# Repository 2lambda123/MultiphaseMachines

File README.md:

# Multiphase-Machine Testbench

This repository contains software code and documentation for deployment at the experiemental multiphase-machine (WICSC) testbench at the SPL at KTH.

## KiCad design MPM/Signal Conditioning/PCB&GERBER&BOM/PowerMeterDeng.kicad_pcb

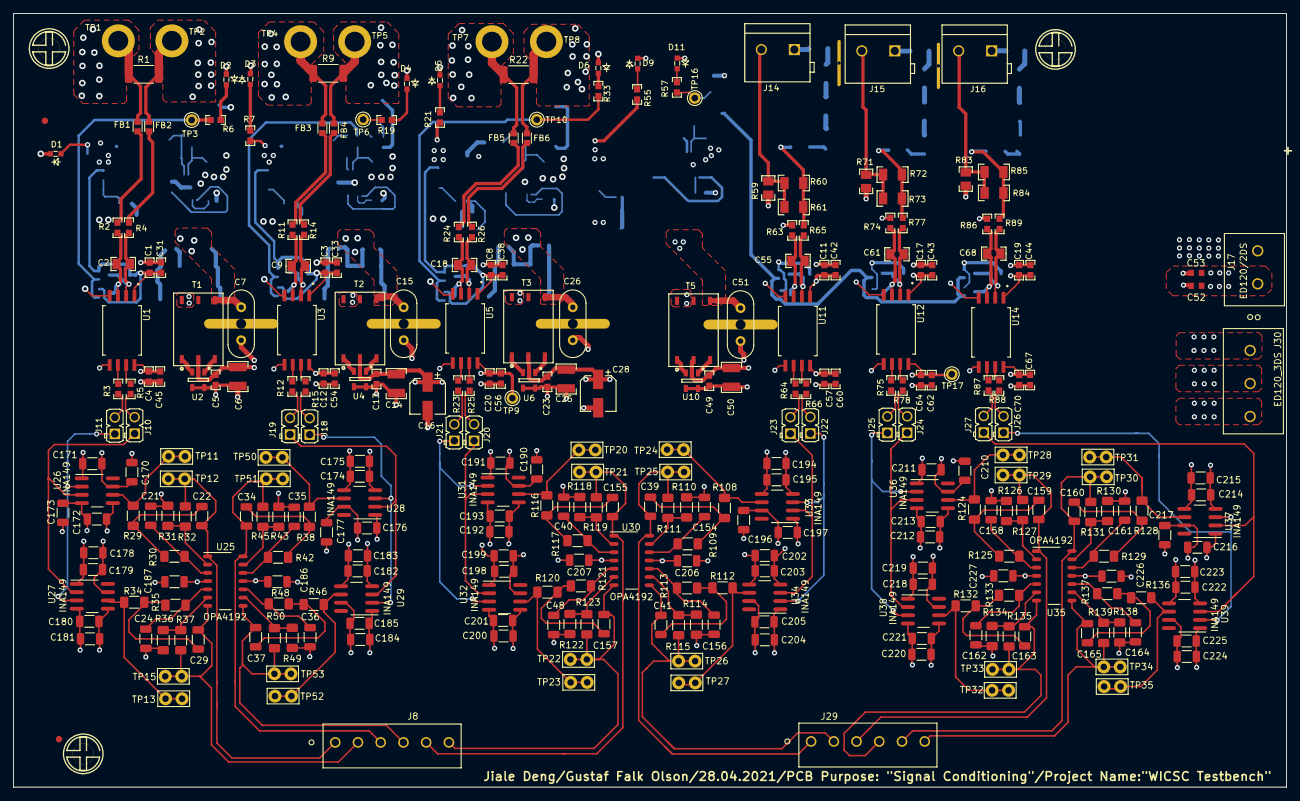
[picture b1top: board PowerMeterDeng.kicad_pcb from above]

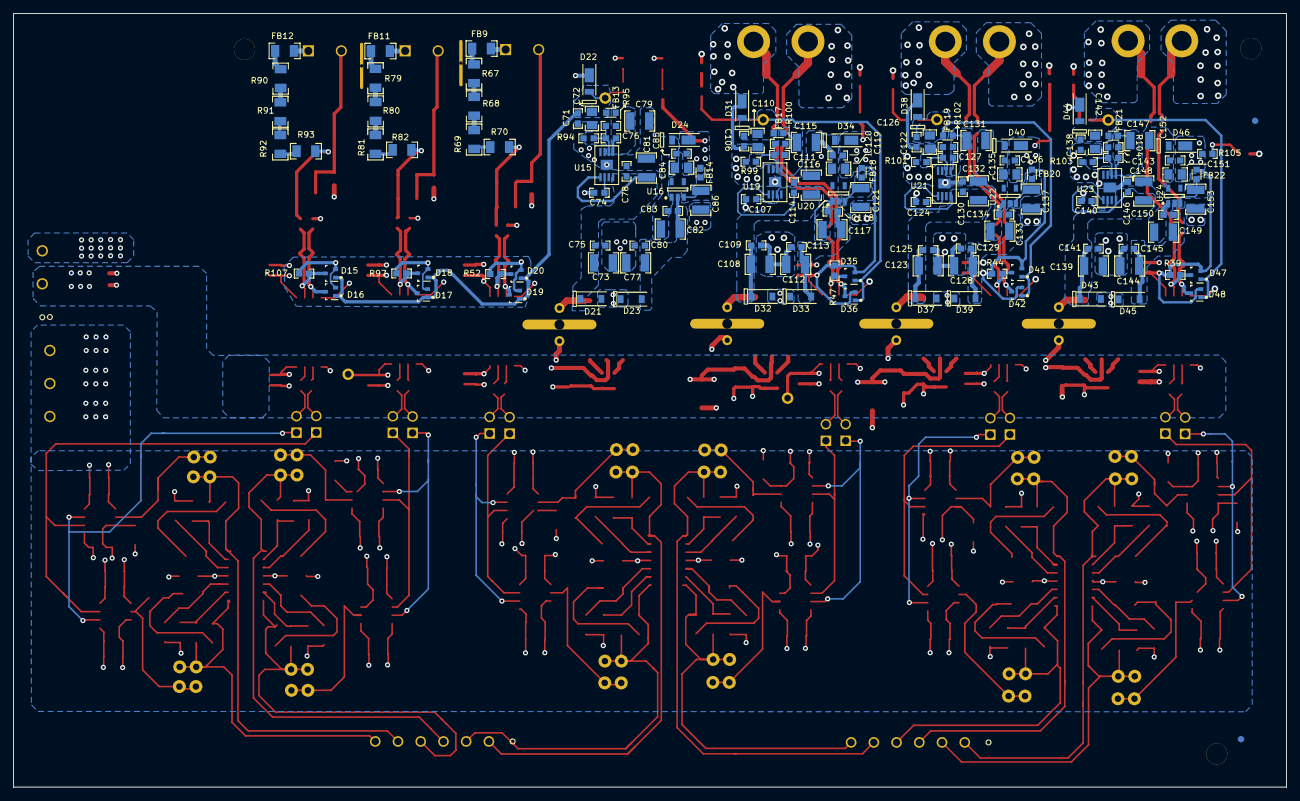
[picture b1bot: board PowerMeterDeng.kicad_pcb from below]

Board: 4 copper layers, 196.0 x 119.1 mm, 459 parts (140 on the bottom side), 197 nets.

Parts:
C1: 0603_19
C2: 08055A331KAT2A; 0805_HV_1
C3: 0603_18
C4: 0603_86
C5: 0603_89
C6: 1210_24
C7: CAP_200mil_2
C8: 0603_87
C9: 08055A331KAT2A; 0805_HV_13
C11: 0603_66
C12: 0603_95
C13: 0603_20
C14: 1210_25
C15: CAP_200mil_3
C16: UUD1E220MCL1GS; SM_RADIAL_5MM_2
C17: 0603_81
C18: 08055A331KAT2A; 0805_HV_15
C19: 0603_88
C20, C64: 0603_63
C21, C24, C35, C36, C40, C48, C154, C156, C158, C161, C162, C164: 100p; C_1206_3216Metric
C22, C29, C34, C37, C155, C157: 105p; C_1206_3216Metric
C23: 0603_13
C25: 1210_2
C26: CAP_200mil_1
C28: UUD1E220MCL1GS; SM_RADIAL_5MM_1
C31: GRM188R71C105KA12D; 0603_10
C33: GRM188R71C105KA12D; 0603_9
C38, C45: GRM188R71C105KA12D; 0603_6
C39, C41, C159, C160, C163, C165: 110p; C_1206_3216Metric
C42, C43: GRM188R71C105KA12D; 0603_8
C44: GRM188R71C105KA12D; 0603_7
C49: 0603_90
C50: 1210_26
C51: CAP_200mil_4
C52: 0.1uF; 06033C104JAT2A
C53: 4.7uF; 0603ZD475KAT2A
C54: GRM188R71C105KA12D; 0603_5
C55: 08055A331KAT2A; 0805_HV_9
C56: GRM188R71C105KA12D; 0603_4
C57: 0603_85
C60: GRM188R71C105KA12D; 0603_3
C61: 08055A331KAT2A; 0805_HV_10
C62: GRM188R71C105KA12D; 0603_2
C67: GRM188R71C105KA12D; 0603_1
C68: 08055A331KAT2A; 0805_HV_11
C70: 0603_67
C71: 0603_40
C72: 0805_HV_6
C73: 1210_23
C74: 0603_41
C75, C80, C83: 0603_31
C76: 0603_8
C77: 1210_22
C78: 0603_38
C79: 1210_17
C81: 1210_16
C82: 1210_18
C84: 0805_HV_7
C85: 0603_42
C86: 1210_19
C106, C145, C150: 0603_16
C107: 0603_100
C108: 1210_21
C109: 0603_60
C110: 0805_HV_17
C111: 0603_99
C112: 1210_3
C113: 0603_62
C114: 0603_98
C115: 1210_27
C116: 1210_20
C117: 1210_28
C118: 0603_102
C119: 0805_HV_18
C120: 0603_101
C121: 1210_29
C122: 0603_34
C123: 1210_7
C124: 0603_35
C125: 0603_22
C126: 0805_HV_4
C127: 0603_33
C128: 1210_5
C129: 0603_17
C130: 0603_32
C131: 1210_13
C132: 1210_12
C133: 1210_14
C134: 0603_37
C135: 0805_HV_5
C136: 0603_36
C137: 1210_15
C138: 0603_25
C139: 1210_6
C140: 0603_26
C141: 0603_21
C142: 0805_HV_2
C143: 0603_24
C144: 1210_4
C146: 0603_23
C147: 1210_9
C148: 1210_8
C149: 1210_10
C151: 0805_HV_3
C152: 0603_27
C153: 1210_11
C170, C173, C175, C176, C178, C181, C182, C184, C186, C187, C190, C193, C195, C196, C198, C201, C202, C204, C206, C207, C210, C213, C215, C216, C218, C221, C222, C224, C226, C227: 100nF; C_1206_3216Metric
C171, C172, C174, C177, C179, C180, C183, C185, C191, C192, C194, C197, C199, C200, C203, C205, C211, C212, C214, C217, C219, C220, C223, C225: 1uF; C_1206_3216Metric
D1: LED0603AA_3
D2: LED0603AA_1
D3: LED0603AA_5
D4: LED0603AA_4
D5: LED0603AA_9
D6: LED0603AA_2
D9: LED0603AA_7
D11: LED0603AA_6
D15: SOT-323_11
D16: SOT-323_12
D17: SOT-323_8
D18: SOT-323_6
D19: SOT-323_7
D20: SOT-323_5
D21: MBR0520L; SOD-123_8
D22: powerDI123_6
D23: MBR0520L; SOD-123_7
D24: powerDI123_7
D31: powerDI123_1
D32: MBR0520L; SOD-123_2
D33: MBR0520L; SOD-123_1
D34: powerDI123_8
D35: SOT-323_2
D36: SOT-323_1
D37: MBR0520L; SOD-123_6
D38: powerDI123_4
D39: MBR0520L; SOD-123_5
D40: powerDI123_5
D41: SOT-323_9
D42: SOT-323_10
D43: MBR0520L; SOD-123_4
D44: powerDI123_2
D45: MBR0520L; SOD-123_3
D46: powerDI123_3
D47: SOT-323_3
D48: SOT-323_4
FB1: MMZ1608B102C; FB0603_8
FB2, FB3, FB4: MMZ1608B102C; FB0603_9
FB5: MMZ1608B102C; FB0603_11
FB6: MMZ1608B102C; FB0603_10
FB9: ERJ-8ENF3323V; 1206_2
FB11: ERJ-8ENF3323V; 1206_3
FB12: ERJ-8ENF3323V; 1206_4
FB13: FB0603_6
FB14: FB0603_7
FB17: FB0603_1
FB18: FB0603_12
FB19: FB0603_4
FB20: FB0603_5
FB21: FB0603_2
FB22: FB0603_3
FID1, FID2, FID5, FID6: Fiducial10-20_1
J8, J29: Conn_01x06; ED555&slash_6DS
J10, J22, J23, J24, J25, J26, J27: 61300211121; WURTH_61300211121_1
J11: 61300211121; WURTH_61300211121_6
J14: ED120/2DS; CONN_ED120-2DS_2
J15: ED120/2DS; CONN_ED120-2DS_3
J16: ED120/2DS; CONN_ED120-2DS_1
J17: ED120/2DS; ED120&slash_2DS
J18: 61300211121; WURTH_61300211121_5
J19: 61300211121; WURTH_61300211121_4
J20: 61300211121; WURTH_61300211121_3
J21: 61300211121; WURTH_61300211121_2
J30: ED120_3DS; ED120&slash_3DS
LOGO1: TI_STACKED_SOLDERMASK_SMALL_1
MH1, MH2, MH3: MH3.2_1
R1, R9, R22: R_2010_5025Metric
R2, R4: RC0603FR-0712RL; 0603_46
R3, R5, R6, R7: 0603_49
R11, R14: RC0603FR-0712RL; 0603_58
R12, R15: 0603_47
R19, R33: 0603_53
R21: 0603_107
R23, R25: 0603_44
R24: RC0603FR-0712RL; 0603_91
R26: RC0603FR-0712RL; 0603_59
R29, R34, R38, R46, R116, R120: 3.01k; R_1206_3216Metric_Pad1.30x1.75mm_HandSolder
R30, R35, R42, R48, R117, R121: 16.5k; R_1206_3216Metric_Pad1.30x1.75mm_HandSolder
R31, R36, R43, R49, R118, R122: 2.49k; R_1206_3216Metric_Pad1.30x1.75mm_HandSolder
R32, R37, R45, R50, R119, R123: 7.5k; R_1206_3216Metric_Pad1.30x1.75mm_HandSolder
R39, R97: CRCW0603160KFKEA; 0603_53
R44: CRCW0603160KFKEA; 0603_8
R47: CRCW0603160KFKEA; 0603_82
R52: CRCW0603160KFKEA; 0603_111
R55, R75, R87, R88: 0603_57
R57: 0603_55
R59: CRCW08050000Z0EA; 0805_HV_8
R60: RC1206FR-071K02L; 1206_8
R61: RC1206FR-072K4L; 1206_9
R63, R65, R77: RC0603FR-0712RL; 0603_64
R64, R66, R78: 0603_64
R67: ERJ-8ENF3323V; 1206_1
R68: ERJ-8ENF3323V; 1206_5
R69: ERJ-8ENF3323V; 1206_6
R70: ERJ-8ENF3323V; 1206_7
R71: CRCW08050000Z0EA; 0805_HV_12
R72: RC1206FR-071K02L; 1206_14
R73: RC1206FR-072K4L; 1206_15
R74: RC0603FR-0712RL; 0603_57
R79: ERJ-8ENF3323V; 1206_10
R80: ERJ-8ENF3323V; 1206_11
R81: ERJ-8ENF3323V; 1206_12
R82: ERJ-8ENF3323V; 1206_13
R83: CRCW08050000Z0EA; 0805_HV_16
R84: RC1206FR-071K02L; 1206_20
R85: RC1206FR-072K4L; 1206_7
R86: RC0603FR-0712RL; 0603_92
R89: RC0603FR-0712RL; 0603_65
R90: ERJ-8ENF3323V; 1206_16
R91: ERJ-8ENF3323V; 1206_17
R92: ERJ-8ENF3323V; 1206_18
R93: ERJ-8ENF3323V; 1206_19
R94: 0603_56
R95: RC0603FR-073K16L; 0603_56
R99: 0603_106
R100: RC0603FR-073K16L; 0603_24
R101: 0603_54
R102: RC0603FR-073K16L; 0603_33
R103: 0603_51
R104: RC0603FR-073K16L; 0603_50
R105: 0603_52
R107: CRCW0603160KFKEA; 0603_112
R108, R112, R124, R128, R132, R136: 1.35k; R_1206_3216Metric_Pad1.30x1.75mm_HandSolder
R109, R113, R125, R129, R133, R137: 17.8k; R_1206_3216Metric_Pad1.30x1.75mm_HandSolder
R110, R114, R126, R130, R134, R138: 500; R_1206_3216Metric_Pad1.30x1.75mm_HandSolder
R111, R115, R127, R131, R135, R139: 4k; R_1206_3216Metric_Pad1.30x1.75mm_HandSolder
T1: 750342271; 760390015_2
T2: 750342271; 760390015_3
T3: 750342271; 760390015_1
T5: 750342271; 760390015_4
TP1: TP-5001-BLACK; TH-40_2
TP2: TP-5001-BLACK; TH-40_1
TP3: TP-040_RND_1
TP4: TP-5001-BLACK; TH-40_4
TP5: TP-5001-BLACK; TH-40_3
TP6: TP-040_RND_2
TP7: TP-5001-BLACK; TH-40_6
TP8: TP-5001-BLACK; TH-40_5
TP9: TP-040_RND_5
TP10: TP-040_RND_4
TP11, TP12, TP13, TP15, TP20, TP21, TP22, TP23, TP24, TP25, TP26, TP27, TP28, TP29, TP30, TP31, TP32, TP33, TP34, TP35, TP50, TP51, TP52, TP53: TestPoint_Bridge_Pitch2.54mm_Drill1.0mm
TP16: TP-040_RND_3
TP17: TP-040_RND_6
U1, U3, U5, U11, U12, U14: AMC1300BDWVR
U2: SN6501DBV; DBV0005A_N_5
U4: SN6501DBV; DBV0005A_N_6
U6: SN6501DBV; DBV0005A_N_4
U10: SN6501DBV; DBV0005A_N_7
U15: MSOP8(DGN)_4
U16: TLV70450DBV; DBV0005A_N_3
U19: MSOP8(DGN)_1
U20: TLV70450DBV; DBV0005A_N_8
U21: MSOP8(DGN)_3
U22: TLV70450DBV; DBV0005A_N_2
U23: TPS7A3001DGNR; MSOP8(DGN)_2
U24: TLV70450DBV; DBV0005A_N_1
U25, U30, U35: OPA4192; OPA4192ID
U26, U27, U28, U29, U31, U32, U33, U34, U36, U37, U38, U39: INA149; INA149AIDR

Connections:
+5.0V_PH: C11.1, C17.1, C19.1, C42.2, C43.2, C44.2, C84.2, C85.1, D15.2, D16.2, D17.2, D18.2, D19.2, D20.2, D24.1, FB14.2, R52.2, R55.2, R97.2, R107.2, U11.1, U12.1, U14.1
+5.0V_USH: C1.1, C31.2, C151.2, C152.1, D46.1, D47.2, D48.2, FB22.2, R39.2, R105.2, U1.1
+5.0V_VSH: C3.1, C33.2, C135.2, C136.1, D40.1, D41.2, D42.2, FB20.2, R7.2, R44.2, U3.1
+5.0V_WSH: C8.1, C38.2, C119.2, C120.1, D34.1, D35.2, D36.2, FB18.2, R21.2, R47.2, U5.1
+5V_CNTL: C5.2, C6.2, C13.2, C14.2, C16.1, C23.2, C25.2, C28.1, C49.2, C50.2, C52.1, C53.1, J17.1, T1.2, T2.2, T3.2, T5.2, U2.2, U4.2, U6.2, U10.2
+6V_PH: C77.1, C80.1, C82.2, C83.1, D23.1, U16.2
+6V_USH: C144.1, C145.1, C149.2, C150.1, D45.1, U24.2
+6V_VSH: C128.1, C129.1, C133.2, C134.1, D39.1, U22.2
+6V_WSH: C112.1, C113.1, C117.2, C118.1, D33.1, U20.2
+15V: C172.1, C173.1, C174.1, C175.1, C180.1, C181.1, C182.1, C183.1, C187.1, C192.1, C193.1, C194.1, C195.1, C200.1, C201.1, C202.1, C203.1, C207.1, C212.1, C213.1, C214.1, C215.1, C220.1, C221.1, C222.1, C223.1, C227.1, J30.1, U25.4 (V+), U26.4, U27.4, U28.4, U29.4, U30.4 (V+), U31.4, U32.4, U33.4, U34.4, U35.4 (V+), U36.4, U37.4, U38.4, U39.4
-5.0V_PH: C71.1, C72.2, D15.1, D16.1, D17.1, D18.1, D19.1, D20.1, D22.2, FB13.2, R57.2, TP16.1
-5.0V_USH: C138.1, C142.2, D44.2, D47.1, D48.1, FB21.2, R6.2, TP3.1
-5.0V_VSH: C122.1, C126.2, D38.2, D41.1, D42.1, FB19.2, R19.2, TP6.1
-5.0V_WSH: C106.1, C110.2, D31.2, D35.1, D36.1, FB17.2, R33.2, TP10.1
-6V_PH: C73.2, C75.2, C78.1, C81.2, D21.2, U15.5, U15.8
-6V_USH: C139.2, C141.2, C146.1, C148.2, D43.2, U23.5, U23.8
-6V_VSH: C123.2, C125.2, C130.1, C132.2, D37.2, U21.5, U21.8
-6V_WSH: C108.2, C109.2, C114.1, C116.2, D32.2, U19.5, U19.8
-15V: C170.1, C171.1, C176.1, C177.1, C178.1, C179.1, C184.1, C185.1, C186.2, C190.1, C191.1, C196.1, C197.1, C198.1, C199.1, C204.1, C205.1, C206.2, C210.1, C211.1, C216.1, C217.1, C218.1, C219.1, C224.1, C225.1, C226.2, J30.3, U25.11 (V-), U26.7, U27.7, U28.7, U29.7, U30.11 (V-), U31.7, U32.7, U33.7, U34.7, U35.11 (V-), U36.7, U37.7, U38.7, U39.7
AMC_VCC: C4.2, C12.2, C20.2, C45.1, C52.2, C53.2, C54.1, C56.1, C57.2, C60.1, C62.1, C64.2, C67.1, C70.2, TP9.1, TP17.1, U1.8, U3.8, U5.8, U11.8, U12.8, U14.8
DGND: C4.1, C5.1, C6.1, C7.1, C12.1, C13.1, C14.1, C15.1, C16.2, C20.1, C21.2, C23.1, C24.2, C25.1, C26.1, C28.2, C35.2, C36.2, C40.2, C45.2, C48.2, C49.1, C50.1, C51.1, C54.2, C56.2, C57.1, C60.2, C62.2, C64.1, C67.2, C70.1, C154.2, C156.2, C158.2, C161.2, C162.2, C164.2, C170.2, C171.2, C172.2, C173.2, C174.2, C175.2, C176.2, C177.2, C178.2, C179.2, C180.2, C181.2, C182.2, C183.2, C184.2, C185.2, C186.1, C187.2, C190.2, C191.2, C192.2, C193.2, C194.2, C195.2, C196.2, C197.2, C198.2, C199.2, C200.2, C201.2, C202.2, C203.2, C204.2, C205.2, C206.1, C207.2, C210.2, C211.2, C212.2, C213.2, C214.2, C215.2, C216.2, C217.2, C218.2, C219.2, C220.2, C221.2, C222.2, C223.2, C224.2, C225.2, C226.1, C227.2, J17.2, J30.2, R31.1, R36.2, R43.2, R49.1, R110.1, R114.2, R118.2, R122.1, R126.1, R130.2, R134.2, R138.1, U1.5, U2.4, U2.5, U3.5, U4.4, U4.5, U5.5, U6.4, U6.5, U10.4, U10.5, U11.5, U12.5, U14.5, U26.1, U26.5, U27.1, U27.5, U28.1, U28.5, U29.1, U29.5, U31.1, U31.5, U32.1, U32.5, U33.1, U33.5, U34.1, U34.5, U36.1, U36.5, U37.1, U37.5, U38.1, U38.5, U39.1, U39.5
DOUTN_CH_U: J11.1, U26.2 (-), U27.3 (+)
DOUTN_CH_U1: J11.2, R3.2
DOUTN_CH_V: J19.1, U28.2 (-), U29.3 (+)
DOUTN_CH_V1: J19.2, R12.2
DOUTN_CH_W: J21.1, U31.2 (-), U32.3 (+)
DOUTN_CH_W1: J21.2, R23.2
DOUTN_U_PH: J23.1, U33.2 (-), U34.3 (+)
DOUTN_U_PH1: J23.2, R64.2
DOUTN_V_PH: J25.1, U36.2 (-), U38.3 (+)
DOUTN_V_PH1: J25.2, R75.2
DOUTN_W_PH: J27.1, U37.2 (-), U39.3 (+)
DOUTN_W_PH1: J27.2, R87.2
DOUTP_CH_U: J10.1, U26.3 (+), U27.2 (-)
DOUTP_CH_U1: J10.2, R5.2
DOUTP_CH_V: J18.1, U28.3 (+), U29.2 (-)
DOUTP_CH_V1: J18.2, R15.2
DOUTP_CH_W: J20.1, U31.3 (+), U32.2 (-)
DOUTP_CH_W1: J20.2, R25.2
DOUTP_U_PH: J22.1, U33.3 (+), U34.2 (-)
DOUTP_U_PH1: J22.2, R66.2
DOUTP_V_PH: J24.1, U36.3 (+), U38.2 (-)
DOUTP_V_PH1: J24.2, R78.2
DOUTP_W_PH: J26.1, U37.3 (+), U39.2 (-)
DOUTP_W_PH1: J26.2, R88.2
GND_PH: C11.2, C17.2, C19.2, C42.1, C43.1, C44.1, C51.2, C71.2, C72.1, C73.1, C74.1, C75.1, C77.2, C78.2, C79.1, C80.2, C81.1, C82.1, C83.2, C84.1, C85.2, C86.1, D9.1, D11.2, D22.1, D24.2, R59.2, R63.1, R71.2, R74.1, R83.2, R86.1, R94.1, T5.4, U11.4, U12.4, U14.4, U15.3, U15.4, U15.9, U16.1
GND_USH: C1.2, C7.2, C31.1, C138.2, C139.1, C140.1, C141.1, C142.1, C144.2, C145.2, C146.2, C147.1, C148.1, C149.1, C150.2, C151.1, C152.2, C153.1, D1.1, D2.2, D44.1, D46.2, FB1.1, R1.1, R103.1, T1.4, TP1.1, U1.4, U23.3, U23.4, U23.9, U24.1
GND_VSH: C3.2, C15.2, C33.1, C122.2, C123.1, C124.1, C125.1, C126.1, C128.2, C129.2, C130.2, C131.1, C132.1, C133.1, C134.2, C135.1, C136.2, C137.1, D3.1, D4.2, D38.1, D40.2, FB3.1, R9.1, R101.1, T2.4, TP4.1, U3.4, U21.3, U21.4, U21.9, U22.1
GND_WSH: C8.2, C26.2, C38.1, C106.2, C107.1, C108.1, C109.1, C110.1, C112.2, C113.2, C114.2, C115.1, C116.1, C117.1, C118.2, C119.1, C120.2, C121.1, D5.1, D6.2, D31.1, D34.2, FB5.1, R22.1, R99.1, T3.4, TP7.1, U5.4, U19.3, U19.4, U19.9, U20.1
In_U: C29.1, J8.2, R37.1, TP15.1, U25.7 (OUTB)
In_V: C37.2, J8.4, R50.1, TP53.1, U25.8 (OUTC)
In_W: C157.2, J8.6, R123.2, TP22.1, U30.7 (OUTB)
Ip_U: C22.2, J8.1, R32.1, TP12.1, U25.1 (OUTA)
Ip_V: C34.1, J8.3, R45.1, TP51.1, U25.14 (OUTD)
Ip_W: C155.1, J8.5, R119.2, TP21.1, U30.1 (OUTA)
NEUTRAL: J14.2, J15.2, J16.2, R59.1, R60.1, R61.1, R71.1, R72.1, R73.1, R83.1, R84.1, R85.1
unnamed: C21.1, R30.2, U25.3 (+INA)
unnamed: C22.1, R29.2, R30.1
unnamed: C24.1, R35.1, U25.5 (+INB)
unnamed: C29.2, R34.1, R35.2
unnamed: C34.2, R38.1, R42.2
unnamed: C35.1, R42.1, U25.12 (+IND)
unnamed: C36.1, R48.2, U25.10 (+INC)
unnamed: C37.1, R46.2, R48.1
unnamed: C39.1, R108.2, R109.1
unnamed: C40.1, R117.1, U30.3 (+INA)
unnamed: C41.2, R112.1, R113.2
unnamed: C48.1, R121.2, U30.5 (+INB)
unnamed: C154.1, R109.2, U30.12 (+IND)
unnamed: C155.2, R116.1, R117.2
unnamed: C156.1, R113.1, U30.10 (+INC)
unnamed: C157.1, R120.2, R121.1
unnamed: C158.1, R125.2, U35.3 (+INA)
unnamed: C159.1, R124.2, R125.1
unnamed: C160.2, R128.1, R129.2
unnamed: C161.1, R129.1, U35.12 (+IND)
unnamed: C162.1, R133.1, U35.5 (+INB)
unnamed: C163.2, R132.1, R133.2
unnamed: C164.1, R137.2, U35.10 (+INC)
unnamed: C165.1, R136.2, R137.1
unnamed: R29.1, TP11.1, U26.6
unnamed: R31.2, R32.2, U25.2 (-INA)
unnamed: R34.2, TP13.1, U27.6
unnamed: R36.1, R37.2, U25.6 (-INB)
unnamed: R38.2, TP50.1, U28.6
unnamed: R43.1, R45.2, U25.13 (-IND)
unnamed: R46.1, TP52.1, U29.6
unnamed: R49.2, R50.2, U25.9 (-INC)
unnamed: R108.1, TP24.1, U33.6
unnamed: R110.2, R111.1, U30.13 (-IND)
unnamed: R112.2, TP27.1, U34.6
unnamed: R114.1, R115.1, U30.9 (-INC)
unnamed: R116.2, TP20.1, U31.6
unnamed: R118.1, R119.1, U30.2 (-INA)
unnamed: R120.1, TP23.1, U32.6
unnamed: R122.2, R123.1, U30.6 (-INB)
unnamed: R124.1, TP28.1, U36.6
unnamed: R126.2, R127.2, U35.2 (-INA)
unnamed: R128.2, TP31.1, U37.6
unnamed: R130.1, R131.2, U35.13 (-IND)
unnamed: R132.2, TP32.1, U38.6
unnamed: R134.1, R135.2, U35.6 (-INB)
unnamed: R136.1, TP35.1, U39.6
unnamed: R138.2, R139.2, U35.9 (-INC)
NetC2_1: C2.1, D47.3, R4.2, R39.1, U1.2
NetC2_2: C2.2, D48.3, R2.2, U1.3
NetC9_1: C9.1, D41.3, R14.2, R44.1, U3.2
NetC9_2: C9.2, D42.3, R11.2, U3.3
NetC18_1: C18.1, D35.3, R26.2, R47.1, U5.2
NetC18_2: C18.2, D36.3, R24.2, U5.3
NetC55_1: C55.1, D20.3, R52.1, R65.2, U11.2
NetC55_2: C55.2, D19.3, R63.2, U11.3
NetC61_1: C61.1, D18.3, R77.2, R97.1, U12.2
NetC61_2: C61.2, D17.3, R74.2, U12.3
NetC68_1: C68.1, D15.3, R89.2, R107.1, U14.2
NetC68_2: C68.2, D16.3, R86.2, U14.3
NetC74_2: C74.2, U15.6
NetC76_1: C76.1, C79.2, FB13.1, R95.2, U15.1
NetC76_2: C76.2, R94.2, R95.1, U15.2
NetC86_2: C86.2, FB14.1, U16.3
NetC107_2: C107.2, U19.6
NetC111_1: C111.1, R99.2, R100.1, U19.2
NetC111_2: C111.2, C115.2, FB17.1, R100.2, U19.1
NetC121_2: C121.2, FB18.1, U20.3
NetC124_2: C124.2, U21.6
NetC127_1: C127.1, R101.2, R102.1, U21.2
NetC127_2: C127.2, C131.2, FB19.1, R102.2, U21.1
NetC137_2: C137.2, FB20.1, U22.3
NetC140_2: C140.2, U23.6
NetC143_1: C143.1, R103.2, R104.1, U23.2
NetC143_2: C143.2, C147.2, FB21.1, R104.2, U23.1
NetC153_2: C153.2, FB22.1, U24.3
NetD1_2: D1.2, R105.1
NetD2_1: D2.1, R6.1
NetD3_2: D3.2, R7.1
NetD4_1: D4.1, R19.1
NetD5_2: D5.2, R21.1
NetD6_1: D6.1, R33.1
NetD9_2: D9.2, R55.1
NetD11_1: D11.1, R57.1
NetD21_1: D21.1, D23.2, T5.6
NetD32_1: D32.1, D33.2, T3.6
NetD37_1: D37.1, D39.2, T2.6
NetD43_1: D43.1, D45.2, T1.6
NetFB1_2: FB1.2, R2.1
NetFB2_1: FB2.1, R1.2, TP2.1
NetFB2_2: FB2.2, R4.1
NetFB3_2: FB3.2, R11.1
NetFB4_1: FB4.1, R9.2, TP5.1
NetFB4_2: FB4.2, R14.1
NetFB5_2: FB5.2, R24.1
NetFB6_1: FB6.1, R22.2, TP8.1
NetFB6_2: FB6.2, R26.1
NetFB9_1: FB9.1, J14.1
NetFB9_2: FB9.2, R67.1
NetFB11_1: FB11.1, J15.1
NetFB11_2: FB11.2, R79.1
NetFB12_1: FB12.1, J16.1
NetFB12_2: FB12.2, R90.1
NetR3_1: R3.1, U1.6
NetR5_1: R5.1, U1.7
NetR12_1: R12.1, U3.6
NetR15_1: R15.1, U3.7
NetR23_1: R23.1, U5.6
NetR25_1: R25.1, U5.7
NetR60_2: R60.2, R61.2, R65.1, R70.2
NetR64_1: R64.1, U11.6
NetR66_1: R66.1, U11.7
NetR67_2: R67.2, R68.1
NetR68_2: R68.2, R69.1
NetR69_2: R69.2, R70.1
NetR72_2: R72.2, R73.2, R77.1, R82.2
NetR75_1: R75.1, U12.6
NetR78_1: R78.1, U12.7
NetR79_2: R79.2, R80.1
NetR80_2: R80.2, R81.1
NetR81_2: R81.2, R82.1
NetR84_2: R84.2, R85.2, R89.1, R93.2
NetR87_1: R87.1, U14.6
NetR88_1: R88.1, U14.7
NetR90_2: R90.2, R91.1
NetR91_2: R91.2, R92.1
NetR92_2: R92.2, R93.1
NetT1_1: T1.1, U2.3
NetT1_3: T1.3, U2.1
NetT2_1: T2.1, U4.3
NetT2_3: T2.3, U4.1
NetT3_1: T3.1, U6.3
NetT3_3: T3.3, U6.1
NetT5_1: T5.1, U10.3
NetT5_3: T5.3, U10.1
Vn_U: C41.1, J29.2, R115.2, TP26.1, U30.8 (OUTC)
Vn_V: C163.1, J29.4, R135.1, TP33.1, U35.7 (OUTB)
Vn_W: C165.2, J29.6, R139.1, TP34.1, U35.8 (OUTC)
Vp_U: C39.2, J29.1, R111.2, TP25.1, U30.14 (OUTD)
Vp_V: C159.2, J29.3, R127.1, TP29.1, U35.1 (OUTA)
Vp_W: C160.1, J29.5, R131.1, TP30.1, U35.14 (OUTD)

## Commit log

2020-10-09 Removing dummy files and adding Pietro's code
2021-03-01 Uploaded Vivado project for WICSC control
2021-03-01 WICSC Control
2021-03-10 Vivado project for the ZC706 board
2021-03-29 Need to fix a way to have all inputs of deserializer connected to something
2021-03-30 Genreated bitstream (not finalized port mapping)
2021-04-12 ZC706 bitstream generated
2021-04-14 PCB Design files
2021-04-14 Added decoupling capacitor and ground testpoints
    Added decoupling capacitor and grounded test points to optical transmitter board.
    Added "REV 0" to silkscreen of FMC connector board
2021-04-15 Mouser links and minimum order added
    When Elfa and RS did not have the component, Mouser was added.
    The minimum order was added.
2021-04-16 added silkscreen label to ground pads
2021-04-19 Added zener diode and pull down resistor to signals
2021-05-05 Create Signal Conditioning
2021-05-05 Create 11
2021-05-05 Create 1
2021-06-02 Fixed female connectors
2021-07-15 Fixed timing issues within modulator
2021-07-23 Added moving average filter, with 16 stages on adc reading
2021-08-06 Changed standard filter size of moving average filter to zero (no filtering)
2021-08-23 Added I2C Master IP
2021-08-23 Added EnableBoard
2021-08-24 Updated BOM
2021-08-31 Updated Vivado and added Vitis testcode for ADCs
2021-11-26 PCB design for eight phase converter
    This is the PCB design and schematic for an eight phase converter design using the TI Piccolo control stick as the processing unit.
    It contains eight SiC half bridges, SCI, JTAG, CAN-bus.
2024-01-12 Snorkell.ai config file

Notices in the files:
parts and their libraries:
Copyright 2016 Accelerated Designs. All rights reserved.
